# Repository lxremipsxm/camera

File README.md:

# Camera

## Information
1. [Component List and Hardware Notes](HardwareNotes.md)
2. [Schematic Details and Images](camCAD/README.md)

## Use (In Progress)
There are four buttons meant for a user interface

## Personal Note
This is the continuation of my stmcam project that I had been working on for a long time, in [this repository](https://github.com/lxremipsxm/stmcam) if you are interested. The goal of that project was to have a completely naked approach to building this camera, using raw C, no Hardware Abstraction Layer and minimal library usage. It was a very code-centered project, and reasonably so, as I had no electrical knowledge or knowledge of using CAD to build (or at least prototype) PCBs. At the time, I was fully confident I could make this with a perfboard and some solder at home if I had the right components, which I did eventually purchase from Digikey. However, I had selected a board without Parallel Capture/DCMI and tried to work my way around it until the workload became utterly infeasible and would have led to me making a project of subpar quality even if I succeeded. It was incredibly frustrating, but I still haven't given up on this project. This repository is a fresh start, and I am changing my approach. I have a new board planned, I have the incredible resource of KiCAD 10.0, and I have developed the skills to build my own PCBs and print them. Additionally, this time I will not dive headfirst into baremetal programming as much. I will use HAL to make a functional project, and I do eventually have to create my own interface to facilitate the use of a OV7670 library I have found on GitHub, which means I still get to code a solid amount without leaving all of it to HAL. In addition to this, because of the need for fast decision making and tight timing constraints, I will use an RTOS implementation for a multithreaded application.

So here is my camera. I am so much more confident in this project's success.

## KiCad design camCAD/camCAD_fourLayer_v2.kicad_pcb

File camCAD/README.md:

## Component Connections and Layout

### Schematics

#### STM32 Power Requirements Schematic (power_conns.kicad_sch)
This schematic is based off of the power requirements detailed in the [STM32 F405xx/F407xx datasheet](https://www.st.com/content/ccc/resource/technical/document/datasheet/ef/92/76/6d/bb/c2/4f/f7/DM00037051.pdf/files/DM00037051.pdf/jcr:content/translations/en.DM00037051.pdf) and cross-checked with the [ST Application Note AN4488](https://www.alldatasheet.com/datasheet-pdf/view/701384/STMICROELECTRONICS/AN4488.html) for good measure.

#### Power Supply and Charging Schematic (buck.kicad_sch)
This schematic contains all of the circuitry necessary to make charging possible and exposes pins to the battery. It includes connections for a USB-C socket that serves as the charging port for the camera, connections for the Dynamic Power Path Management IC (charging + power management), the buck converter circuitry to efficiently step down the battery's 3.7V to 3.3V, and the battery terminals, which will use an XH socket. (Initially I planned to have the buck converter on a separate schematic, hence the filename, but there wasn't enough detail to justify a separate schematic)

#### Components Schematic (components.kicad_sch)
This schematic contains the component connections that provide all the functionality of a camera. It contains the OV7670 Camera Module, the ILI9341 Display header, activity LEDs, and the MicroSD transflash breakout board.

#### STM32F407 schematic (f407zgt6.kicad_sch)
Contains the STM32F407ZGT6 LPQF144 chip. ~~In the near future I will put more circuits in this schematic, such as the bootloader switch.~~

#### User Interface (user_interface.kicad_sch)
This schematic contains the buttons that will aid the user in communicating with the camera, such as taking pictures, toggling flash, deleting pictures, and navigating saved pictures via a picture menu.

### PCB Layout (Two Layer)
I was recommended to use four layers to separate the ground and VCC Planes better, but this is what I got routing with a two-layer PCB, with the back CU layer housing a ground fill zone. 
The following layout was verified by the DRC. All dimensions are in mm.
| Layout | 3D Model |
| ------- | -------- |
|  |  |

| Back Layout | 3D Model |
| ------- | -------- |
|  | .png) |

### PCB Layout (Four Layer)
This PCB will be printed once I reverify the schematics and layout. I was able to make the board a little more compact with four layers.
The layout was verified by the DRC. All dimensions are in mm.

| Front CU | Back CU |
|-------- | -------- | 
|  |  |
|  |  |

| VCC CU | GND CU |
| ------- | ------- |
|  |  |

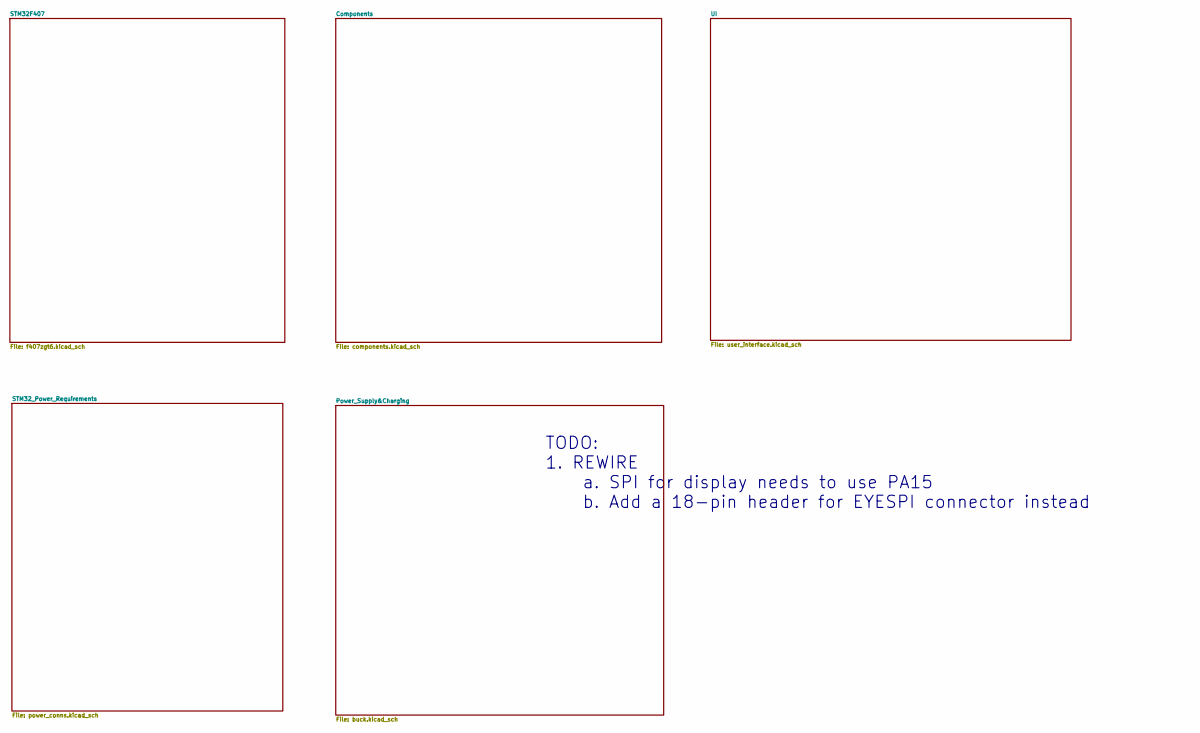
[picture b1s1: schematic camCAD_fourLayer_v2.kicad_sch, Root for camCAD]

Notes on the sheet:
TODO: 1. REWIRE a. SPI for display needs to use PA15 b. Add a 18-pin header for EYESPI connector instead

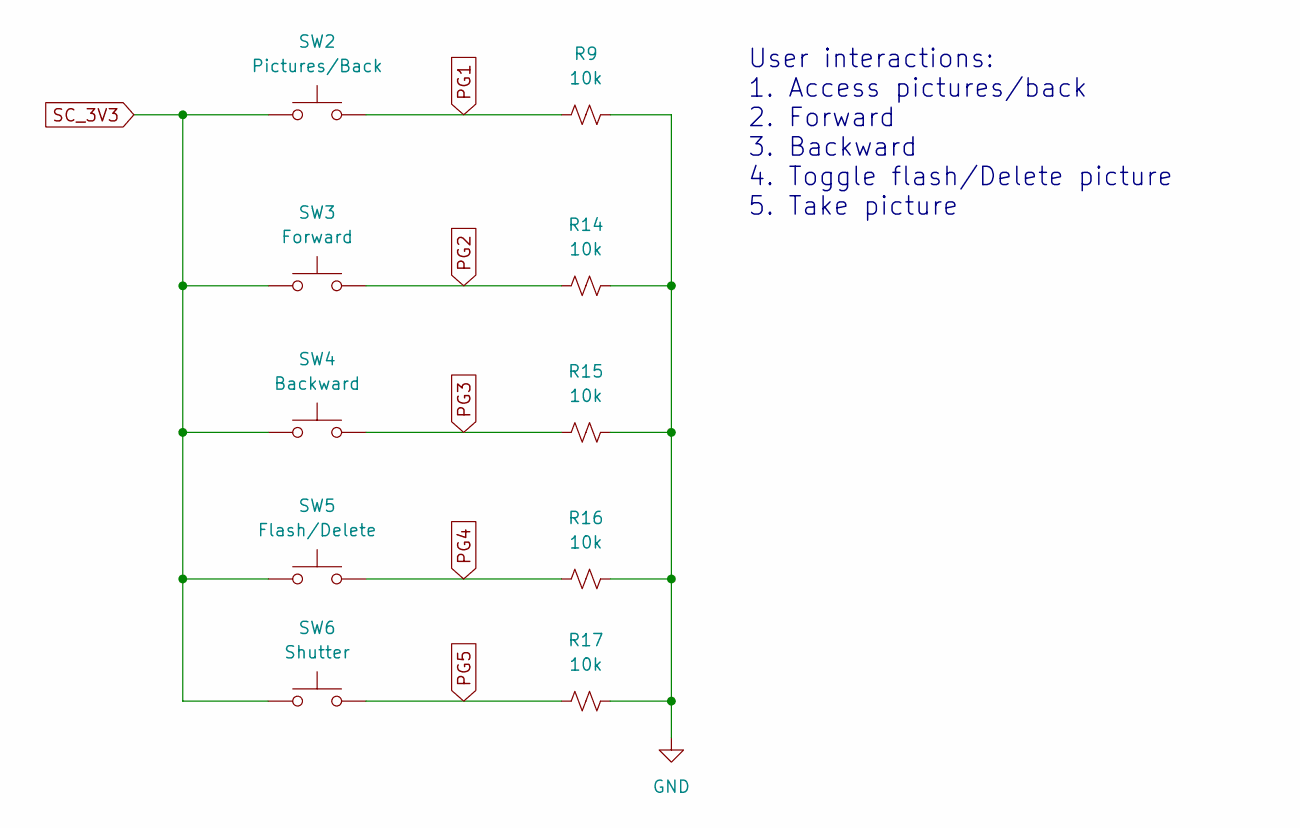
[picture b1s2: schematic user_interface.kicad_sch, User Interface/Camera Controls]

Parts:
R9, R14, R15, R16, R17: 10k; R_0402_1005Metric
SW2: Pictures/Back; SW_SKRPABE010
SW3: Forward; SW_SKRPABE010
SW4: Backward; SW_SKRPABE010
SW5: Flash/Delete; SW_SKRPABE010
SW6: Shutter; SW_SKRPABE010

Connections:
BATT-: R9.2, R14.2, R15.2, R16.2, R17.2; also elsewhere on the board
PG1: R9.1, SW2.2; also elsewhere on the board
PG2: R14.1, SW3.2; also elsewhere on the board
PG3: R15.1, SW4.2; also elsewhere on the board
PG4: R16.1, SW5.2; also elsewhere on the board
PG5: R17.1, SW6.2; also elsewhere on the board
SC_3V3: SW2.1, SW3.1, SW4.1, SW5.1, SW6.1; also elsewhere on the board

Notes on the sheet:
User interactions: 1. Access pictures/back 2. Forward 3. Backward 4. Toggle flash/Delete picture 5. Take picture

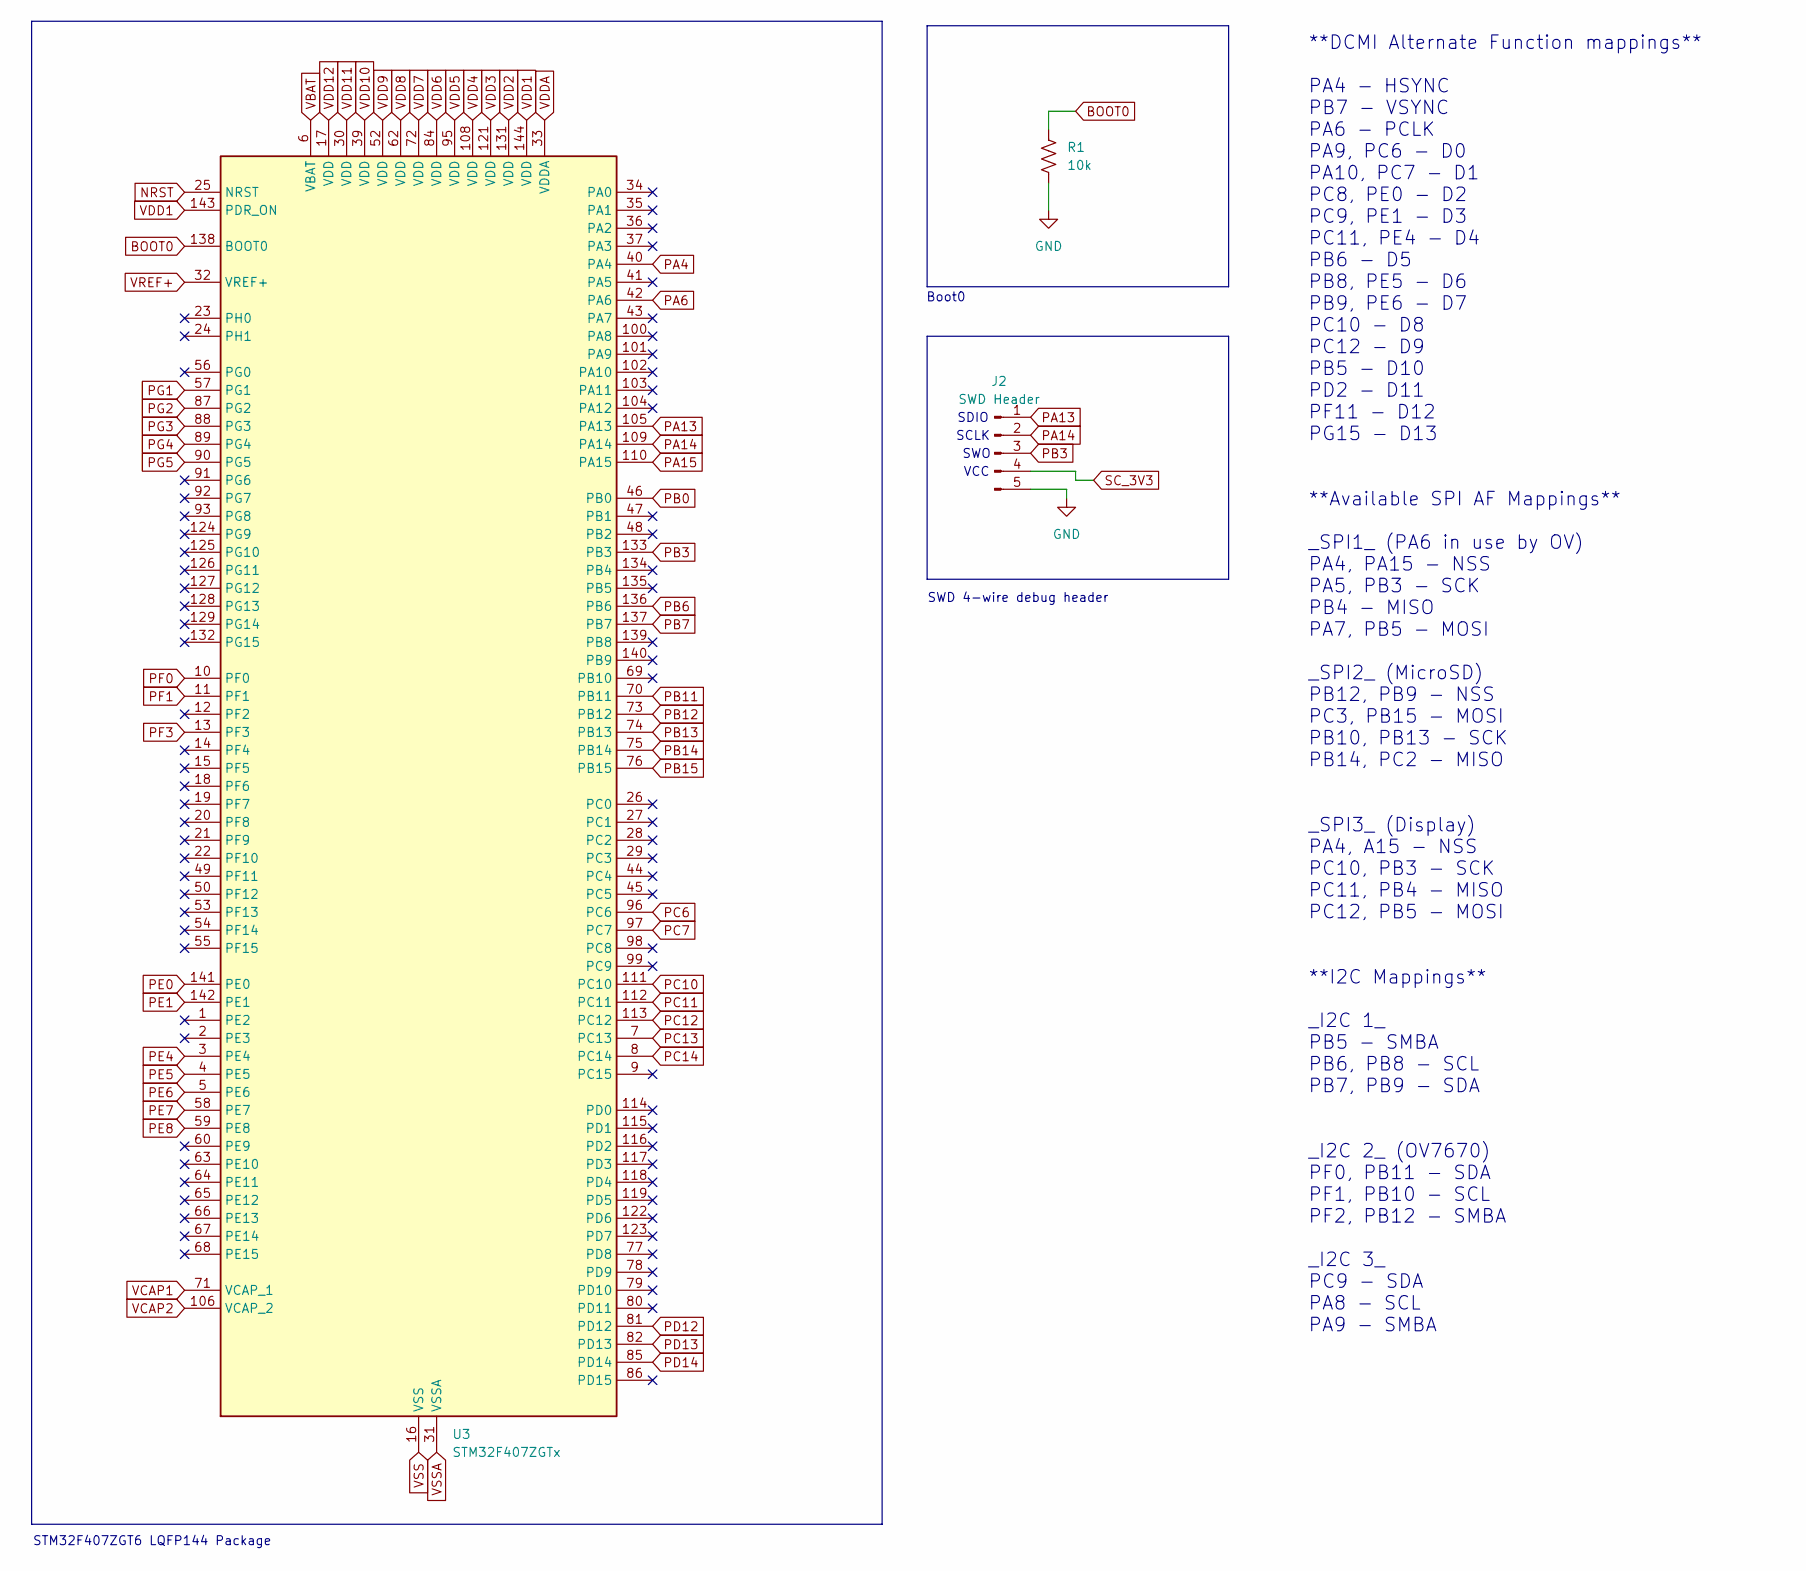
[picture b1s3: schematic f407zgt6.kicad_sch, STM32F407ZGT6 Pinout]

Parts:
J2: SWD Header; PinHeader_1x05_P2.54mm_Vertical
R1: 10k; R_0402_1005Metric
U3: STM32F407ZGTx; LQFP-144_20x20mm_P0.5mm

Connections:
BATT-: J2.5, R1.2, U3.16 (VSS), U3.31 (VSSA), U3.38 (VSS), U3.51 (VSS), U3.61 (VSS), U3.83 (VSS), U3.94 (VSS), U3.107 (VSS), U3.120 (VSS), U3.130 (VSS); also elsewhere on the board
BOOT0: R1.1, U3.138 (BOOT0)
NRST: U3.25 (NRST); also elsewhere on the board
PA4: U3.40 (PA4); also elsewhere on the board
PA6: U3.42 (PA6); also elsewhere on the board
PA13: J2.1, U3.105 (PA13)
PA14: J2.2, U3.109 (PA14)
PA15: U3.110 (PA15); also elsewhere on the board
PB0: U3.46 (PB0); also elsewhere on the board
PB3: J2.3, U3.133 (PB3)
PB6: U3.136 (PB6); also elsewhere on the board
PB7: U3.137 (PB7); also elsewhere on the board
PB11: U3.70 (PB11); also elsewhere on the board
PB12: U3.73 (PB12); also elsewhere on the board
PB13: U3.74 (PB13); also elsewhere on the board
PB14: U3.75 (PB14); also elsewhere on the board
PB15: U3.76 (PB15); also elsewhere on the board
PC6: U3.96 (PC6); also elsewhere on the board
PC7: U3.97 (PC7); also elsewhere on the board
PC10: U3.111 (PC10); also elsewhere on the board
PC11: U3.112 (PC11); also elsewhere on the board
PC12: U3.113 (PC12); also elsewhere on the board
PC13: U3.7 (PC13); also elsewhere on the board
PC14: U3.8 (PC14); also elsewhere on the board
PD12: U3.81 (PD12); also elsewhere on the board
PD13: U3.82 (PD13); also elsewhere on the board
PD14: U3.85 (PD14); also elsewhere on the board
PE0: U3.141 (PE0); also elsewhere on the board
PE1: U3.142 (PE1); also elsewhere on the board
PE4: U3.3 (PE4); also elsewhere on the board
PE5: U3.4 (PE5); also elsewhere on the board
PE6: U3.5 (PE6); also elsewhere on the board
PE7: U3.58 (PE7); also elsewhere on the board
PE8: U3.59 (PE8); also elsewhere on the board
PF0: U3.10 (PF0); also elsewhere on the board
PF1: U3.11 (PF1); also elsewhere on the board
PF3: U3.13 (PF3); also elsewhere on the board
PG1: U3.57 (PG1); also elsewhere on the board
PG2: U3.87 (PG2); also elsewhere on the board
PG3: U3.88 (PG3); also elsewhere on the board
PG4: U3.89 (PG4); also elsewhere on the board
PG5: U3.90 (PG5); also elsewhere on the board
SC_3V3: J2.4, U3.6 (VBAT), U3.17 (VDD), U3.30 (VDD), U3.33 (VDDA), U3.39 (VDD), U3.52 (VDD), U3.62 (VDD), U3.72 (VDD), U3.84 (VDD), U3.95 (VDD), U3.108 (VDD), U3.121 (VDD), U3.131 (VDD), U3.143 (PDR_ON), U3.144 (VDD); also elsewhere on the board
VCAP1: U3.71 (VCAP_1); also elsewhere on the board
VCAP2: U3.106 (VCAP_2); also elsewhere on the board
VREF+: U3.32 (VREF+); also elsewhere on the board

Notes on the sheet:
SCLK
Boot0
**DCMI Alternate Function mappings** PA4 - HSYNC PB7 - VSYNC PA6 - PCLK PA9, PC6 - D0 PA10, PC7 - D1 PC8, PE0 - D2 PC9, PE1 - D3 PC11, PE4 - D4 PB6 - D5 PB8, PE5 - D6 PB9, PE6 - D7 PC10 - D8 PC12 - D9 PB5 - D10 PD2 - D11 PF11 - D12 PG15 - D13 **Available SPI AF Mappings** _SPI1_ (PA6 in use by OV) 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
STM32F407ZGT6 LQFP144 Package
VCC
SWD 4-wire debug header
SDIO
SWO

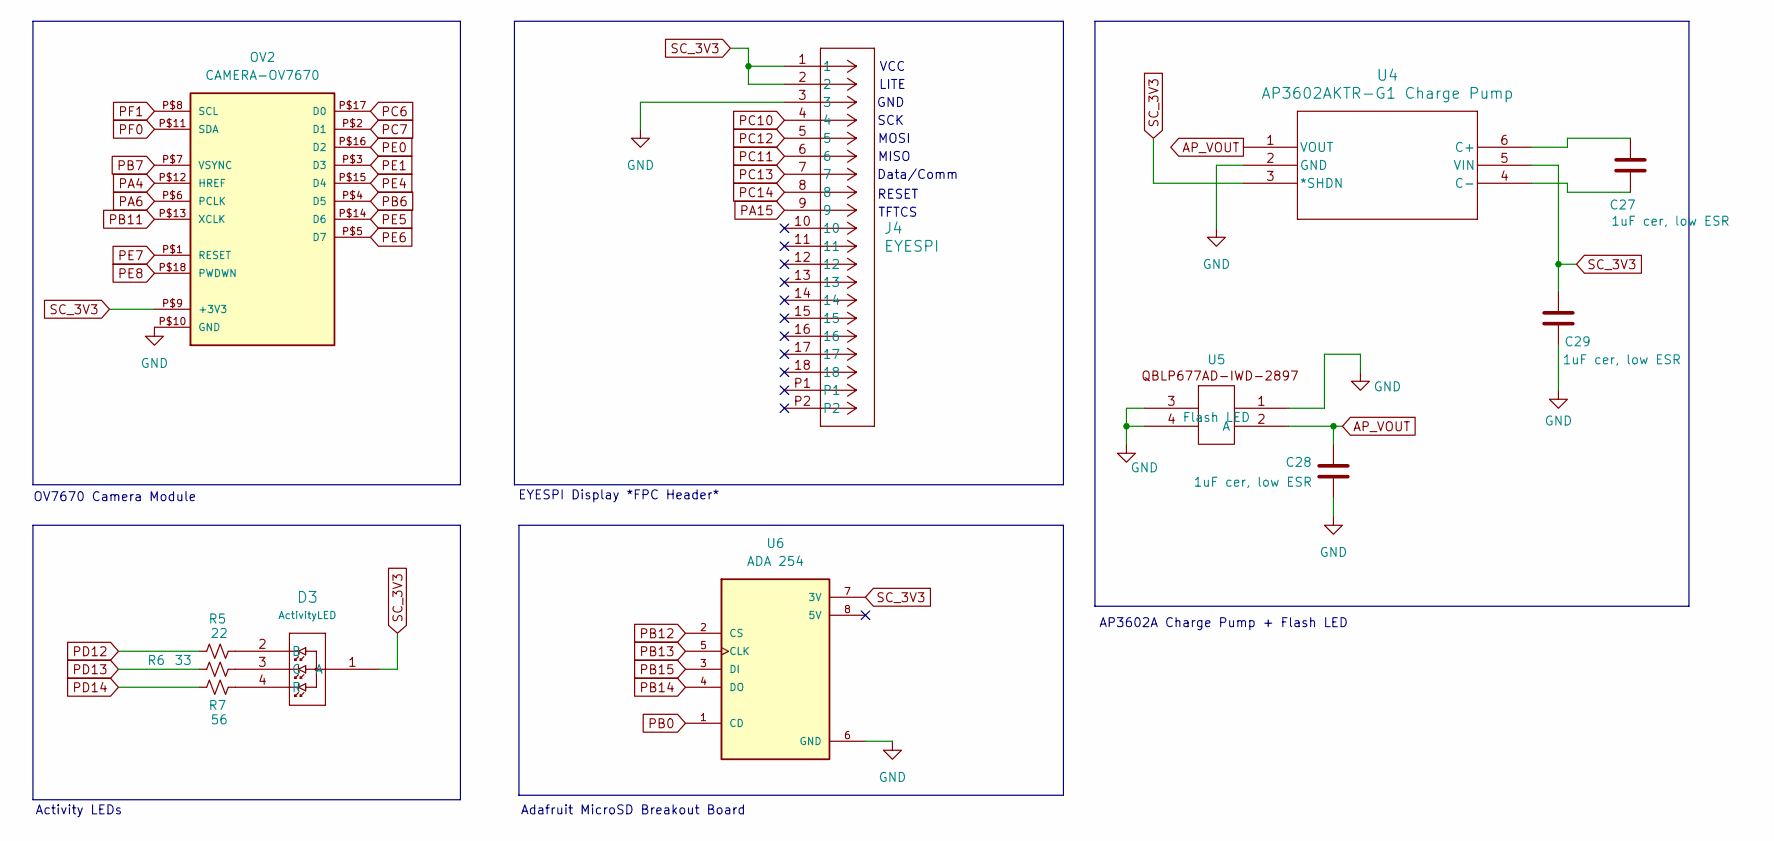
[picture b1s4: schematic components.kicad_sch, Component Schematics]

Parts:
C27, C28, C29: 1uF cer, low ESR; C_0603_1608Metric
D3: ActivityLED; CLMVC-FKA-CL1D1L71BB7C3C3_CRE
J4: EYESPI; CON_5051101892_MOL
OV2: CAMERA-OV7670; CAMERA-OV7670-DIP
R5: 22; R_0402_1005Metric
R6: 33; R_0402_1005Metric
R7: 56; R_0402_1005Metric
U4: AP3602AKTR-G1 Charge Pump; SOT-23-6_DIO
U5: Flash LED; QBLP677AD-IWD-2897
U6: ADA 254; MODULE_254; PARTREV Jul 31, 2013

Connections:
AP_VOUT: C28.1, U4.1 (VOUT), U5.2 (A_2)
BATT-: C28.2, C29.2, J4.3, OV2.P$10 (GND), U4.2 (GND), U5.1, U5.3, U5.4, U6.6 (GND); also elsewhere on the board
unnamed: D3.2 (B), R5.2
unnamed: D3.3 (G), R6.2
unnamed: D3.4 (R), R7.2
unnamed: C27.1, U4.6 (C+)
unnamed: C27.2, U4.4 (C-)
PA4: OV2.P$12 (HREF); also elsewhere on the board
PA6: OV2.P$6 (PCLK); also elsewhere on the board
PA15: J4.9; also elsewhere on the board
PB0: U6.1 (CD); also elsewhere on the board
PB6: OV2.P$4 (D5); also elsewhere on the board
PB7: OV2.P$7 (VSYNC); also elsewhere on the board
PB11: OV2.P$13 (XCLK); also elsewhere on the board
PB12: U6.2 (CS); also elsewhere on the board
PB13: U6.5 (CLK); also elsewhere on the board
PB14: U6.4 (DO); also elsewhere on the board
PB15: U6.3 (DI); also elsewhere on the board
PC6: OV2.P$17 (D0); also elsewhere on the board
PC7: OV2.P$2 (D1); also elsewhere on the board
PC10: J4.4; also elsewhere on the board
PC11: J4.6; also elsewhere on the board
PC12: J4.5; also elsewhere on the board
PC13: J4.7; also elsewhere on the board
PC14: J4.8; also elsewhere on the board
PD12: R5.1; also elsewhere on the board
PD13: R6.1; also elsewhere on the board
PD14: R7.1; also elsewhere on the board
PE0: OV2.P$16 (D2); also elsewhere on the board
PE1: OV2.P$3 (D3); also elsewhere on the board
PE4: OV2.P$15 (D4); also elsewhere on the board
PE5: OV2.P$14 (D6); also elsewhere on the board
PE6: OV2.P$5 (D7); also elsewhere on the board
PE7: OV2.P$1 (RESET); also elsewhere on the board
PE8: OV2.P$18 (PWDWN); also elsewhere on the board
PF0: OV2.P$11 (SDA); also elsewhere on the board
PF1: OV2.P$8 (SCL); also elsewhere on the board
SC_3V3: C29.1, D3.1 (A), J4.1, J4.2, OV2.P$9 (+3V3), U4.3 (*SHDN), U4.5 (VIN), U6.7 (3V); also elsewhere on the board

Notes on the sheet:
AP3602A Charge Pump + Flash LED
EYESPI Display *FPC Header*
MISO
SCK
LITE
RESET
MOSI
Data/Comm
Adafruit MicroSD Breakout Board
VCC
Activity LEDs
TFTCS
GND
OV7670 Camera Module

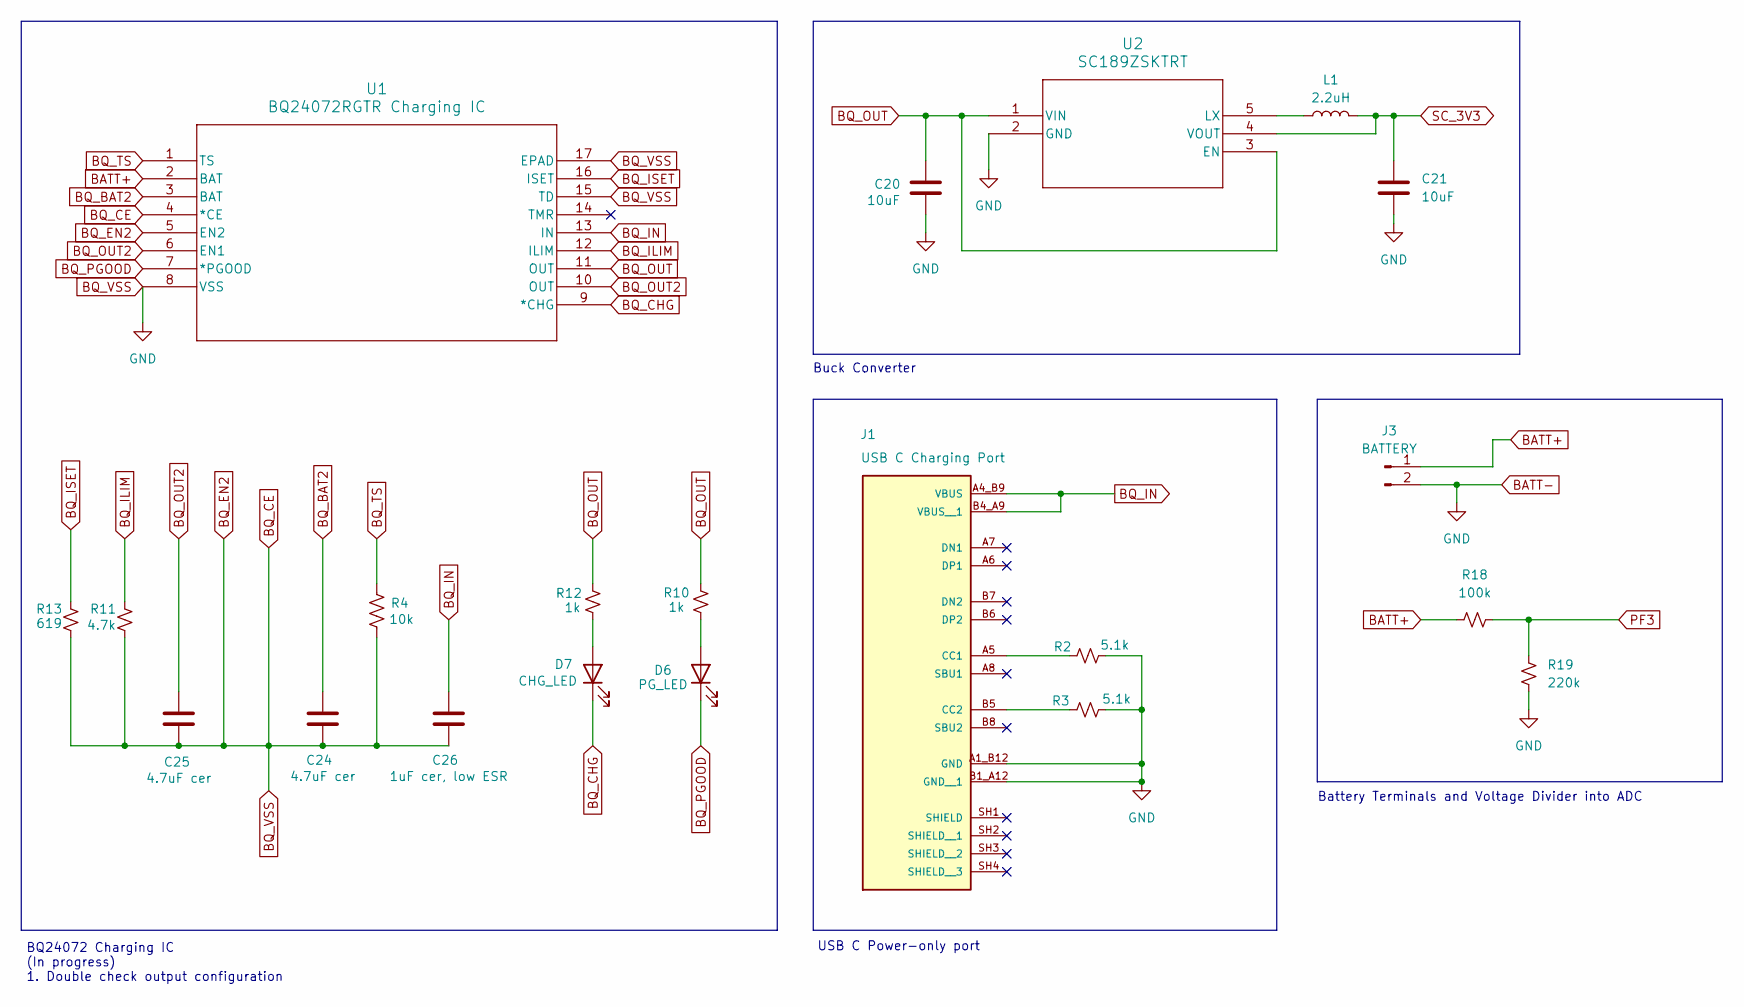
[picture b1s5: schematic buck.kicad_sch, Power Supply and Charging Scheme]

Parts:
C20, C21: 10uF; C_0603_1608Metric
C24, C25: 4.7uF cer; C_0805_2012Metric
C26: 1uF cer, low ESR; C_0603_1608Metric
D6: PG_LED; LEDM1608X80_G
D7: CHG_LED; LEDC1608X35N_R
J1: USB C Charging Port; SAMESKY_UJ20-C-H-G-SMT-1-P16-TR; PARTREV 1.0
J3: BATTERY; JST_B2B-XH-A
L1: 2.2uH; L_1008_2520Metric
R2, R3: 5.1k; R_0402_1005Metric
R4: 10k; R_0402_1005Metric
R10, R12: 1k; R_0402_1005Metric
R11: 4.7k; R_0402_1005Metric
R13: 619; R_0402_1005Metric
R18: 100k; R_0402_1005Metric
R19: 220k; R_0805_2012Metric
U1: BQ24072RGTR Charging IC; RGT16_1P7X1P7
U2: SC189ZSKTRT; SOT23-5-SC189_SEM

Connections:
BATT+: J3.1, R18.1, U1.2 (BAT)
BATT-: C20.2, C21.2, C24.2, C25.2, C26.2, J1.A1_B12 (GND), J1.B1_A12 (GND__1), J3.2, R2.2, R3.2, R4.1, R11.2, R13.2, R19.2, U1.4 (*CE), U1.5 (EN2), U1.8 (VSS), U1.15 (TD), U1.17 (EPAD), U1.V, U2.2 (GND); also elsewhere on the board
BQ_BAT2: C24.1, U1.3 (BAT)
BQ_CHG: D7.C (K), U1.9 (*CHG)
BQ_ILIM: R11.1, U1.12 (ILIM)
BQ_IN: C26.1, J1.A4_B9 (VBUS), J1.B4_A9 (VBUS__1), U1.13 (IN)
BQ_ISET: R13.1, U1.16 (ISET)
BQ_OUT: C20.1, R10.1, R12.1, U1.11 (OUT), U2.1 (VIN), U2.3 (EN)
BQ_OUT2: C25.1, U1.6 (EN1), U1.10 (OUT)
BQ_PGOOD: D6.C (K), U1.7 (*PGOOD)
BQ_TS: R4.2, U1.1 (TS)
unnamed: D6.A, R10.2
unnamed: D7.A, R12.2
unnamed: J1.A5 (CC1), R2.1
unnamed: J1.B5 (CC2), R3.1
unnamed: L1.1, U2.5 (LX)
PF3: R18.2, R19.1; also elsewhere on the board
SC_3V3: C21.1, L1.2, U2.4 (VOUT); also elsewhere on the board

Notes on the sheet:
Battery Terminals and Voltage Divider into ADC
BQ24072 Charging IC (In progress) 1. Double check output configuration
Buck Converter
USB C Power-only port

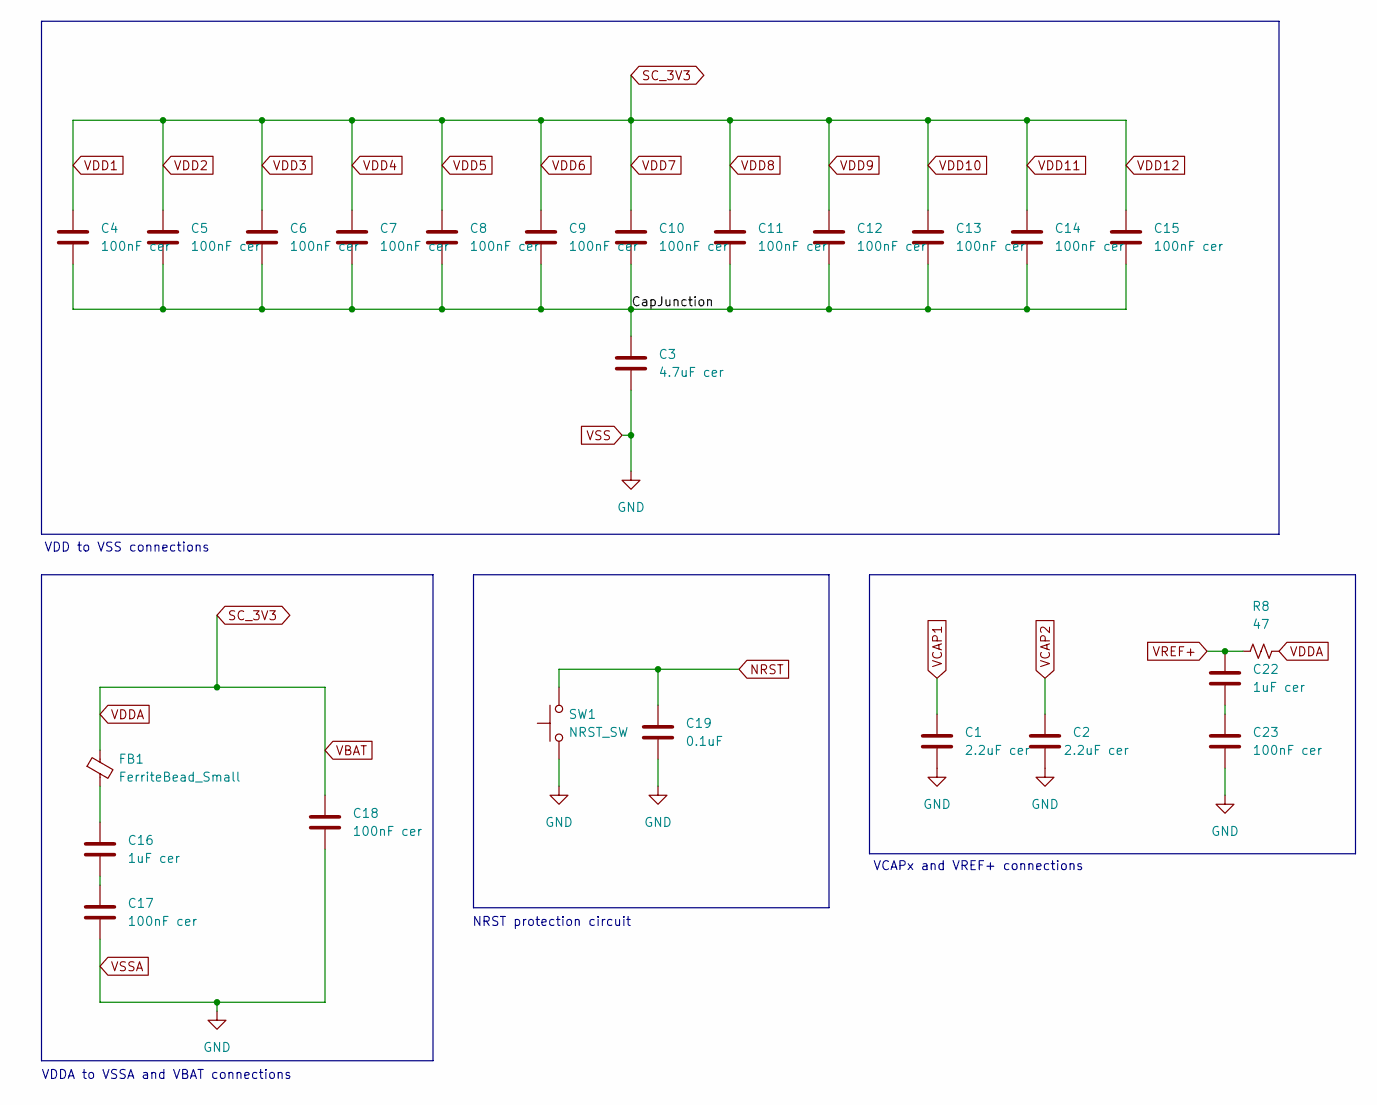
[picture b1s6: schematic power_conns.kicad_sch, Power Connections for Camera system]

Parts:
C1, C2: 2.2uF cer; C_0201_0603Metric
C3: 4.7uF cer; C_0805_2012Metric
C4, C5, C6, C7, C8, C9, C10, C11, C12, C13, C14, C15, C17, C18, C23: 100nF cer; C_0603_1608Metric
C16, C22: 1uF cer; C_0603_1608Metric
C19: 0.1uF; C_0603_1608Metric
FB1: FerriteBead_Small; BEADC1608X95N
R8: 47; R_1206_3216Metric
SW1: NRST_SW; SW_SKRPABE010

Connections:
/STM32_Power_Requirements/CapJunction: C3.1, C4.2, C5.2, C6.2, C7.2, C8.2, C9.2, C10.2, C11.2, C12.2, C13.2, C14.2, C15.2
BATT-: C1.2, C2.2, C3.2, C17.2, C18.2, C19.2, C23.2, SW1.1; also elsewhere on the board
NRST: C19.1, SW1.2; also elsewhere on the board
unnamed: C16.1, FB1.2
unnamed: C16.2, C17.1
unnamed: C22.2, C23.1
SC_3V3: C4.1, C5.1, C6.1, C7.1, C8.1, C9.1, C10.1, C11.1, C12.1, C13.1, C14.1, C15.1, C18.1, FB1.1, R8.2; also elsewhere on the board
VCAP1: C1.1; also elsewhere on the board
VCAP2: C2.1; also elsewhere on the board
VREF+: C22.1, R8.1; also elsewhere on the board

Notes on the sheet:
VDDA to VSSA and VBAT connections
VCAPx and VREF+ connections
NRST protection circuit
VDD to VSS connections

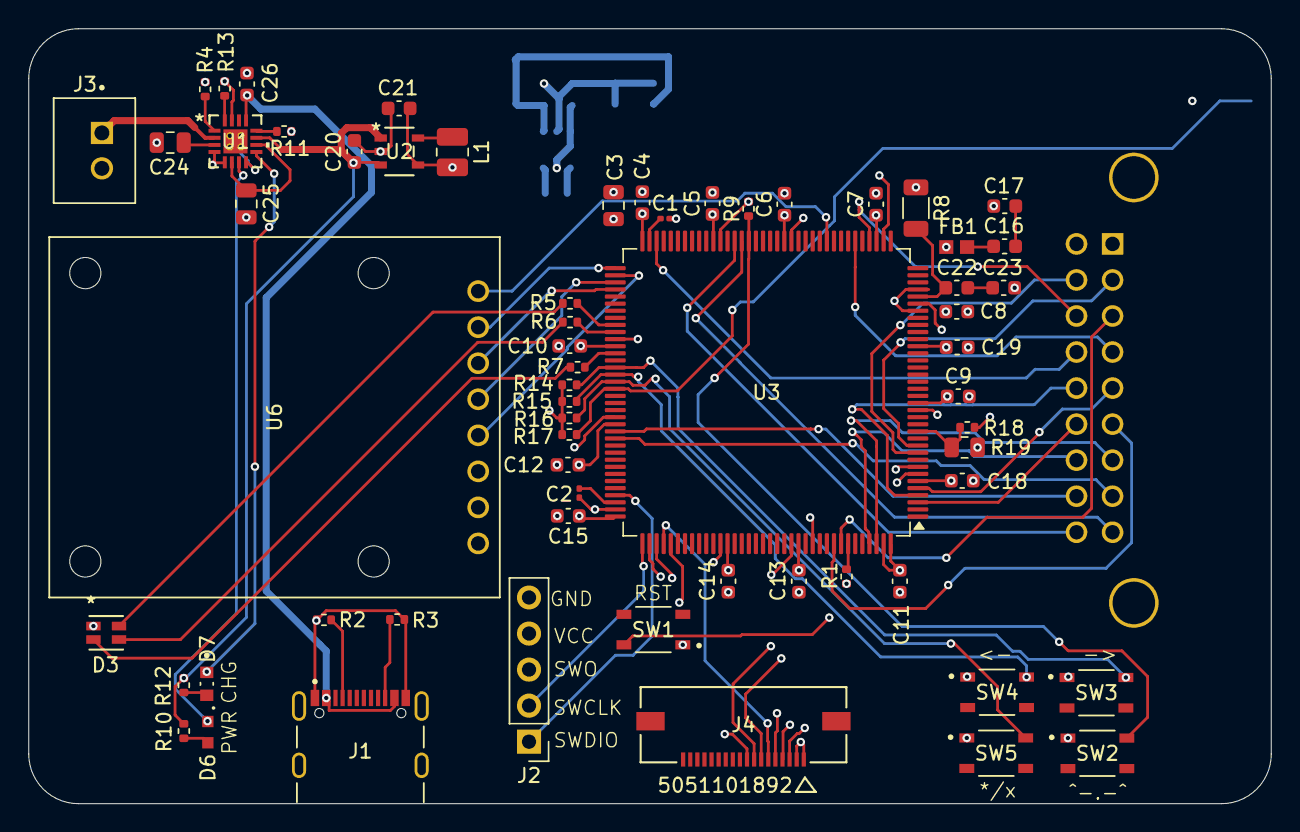
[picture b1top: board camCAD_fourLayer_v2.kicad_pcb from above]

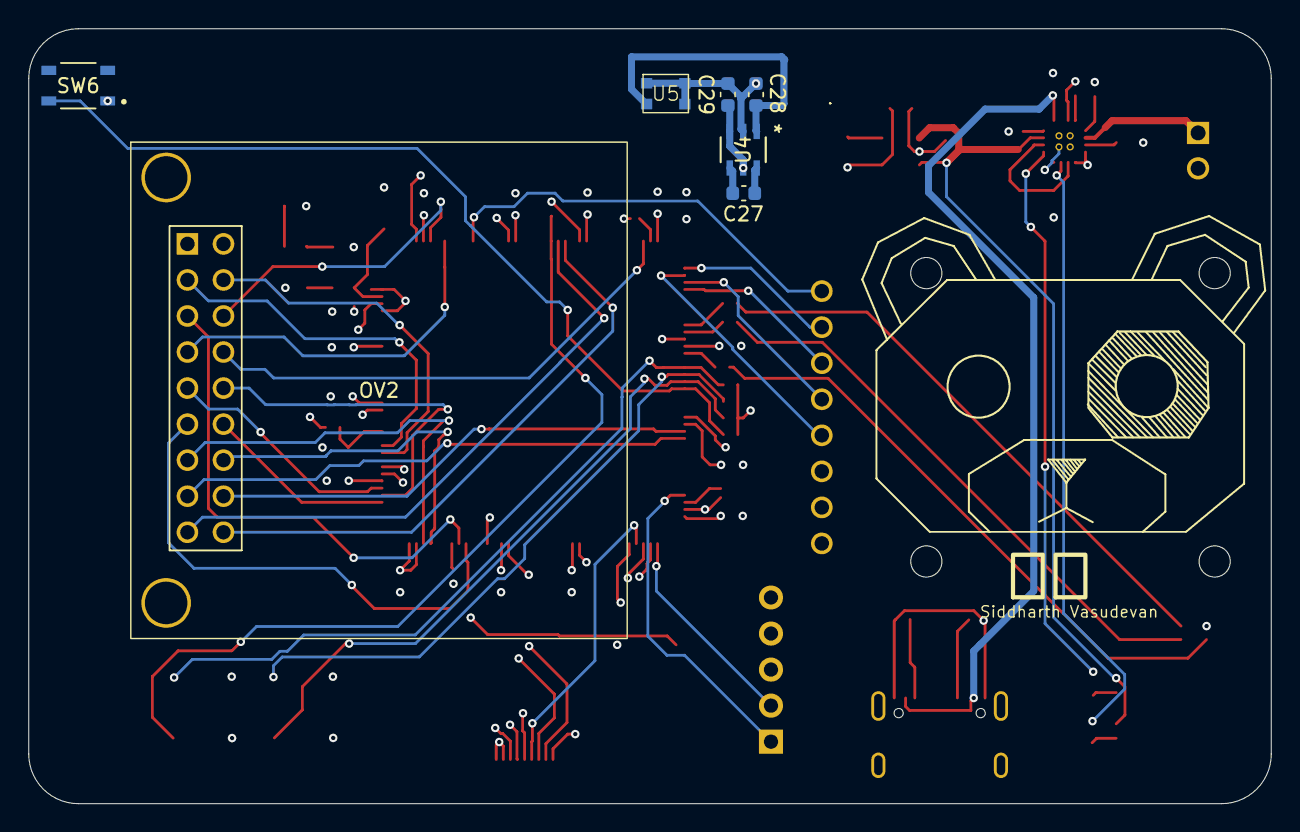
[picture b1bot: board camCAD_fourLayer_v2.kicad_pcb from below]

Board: 4 copper layers, 87.6 x 54.6 mm, 70 parts (7 on the bottom side), 71 nets.

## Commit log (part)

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2026-05-29 First push
2026-05-31 Debug + MicroSD connections complete
2026-06-02 Finished connections for ILI9341, power incomplete
2026-06-05 Push before adding power configuration
2026-06-05 working on power
2026-06-05 restarted power
2026-06-05 removing previous sheet, buggy
2026-06-09 Included buck converter schematic
2026-06-09 restructured hierarchy and cleaned up schematic
2026-06-11 Added battery to HardwareNotes.md, some touch ups on schematic
2026-06-13 Adding charging functionality
